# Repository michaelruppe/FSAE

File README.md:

# FSAE

Hardware projects for the FSAE Electric 2019/2020 competition (Australia).
💻Github https://github.com/michaelruppe/FSAE

## Resources
**Team mentoring and design reviews available - contact through [michaelruppe.com](https://michaelruppe.com)**

[ShutdownCircuit.com](https://shutdowncircuit.com) is a free resource to help new FSAE EV teams shortcut the growing pains of designing EV safety systems.

## [TSAL](TSALv3)
A light that indicates presence of dangerous voltage within the Tractive System

<div align="center">

<p>The third iteration of the TSAL driver. </p>
</div>

Watch a [video walkthrough](https://youtu.be/bgW9xbbovIY) explaining the circuit operation and design decision.

## [Precharge](Precharge)
A device to precharge the Tractive System. This prototype features voltage feedback to protect AIRs. In open-loop systems, if a wiring fault develops - eg. precharge resistor is disconnected - then the precharge is ineffective and AIRs may become damaged.
<div align="center">

<p>The prototype Precharge module</p>
</div>

 ## [HFL (Hard Fault Latch)](HFL)

 Latches momentary faults that are required to shutdown the EV.

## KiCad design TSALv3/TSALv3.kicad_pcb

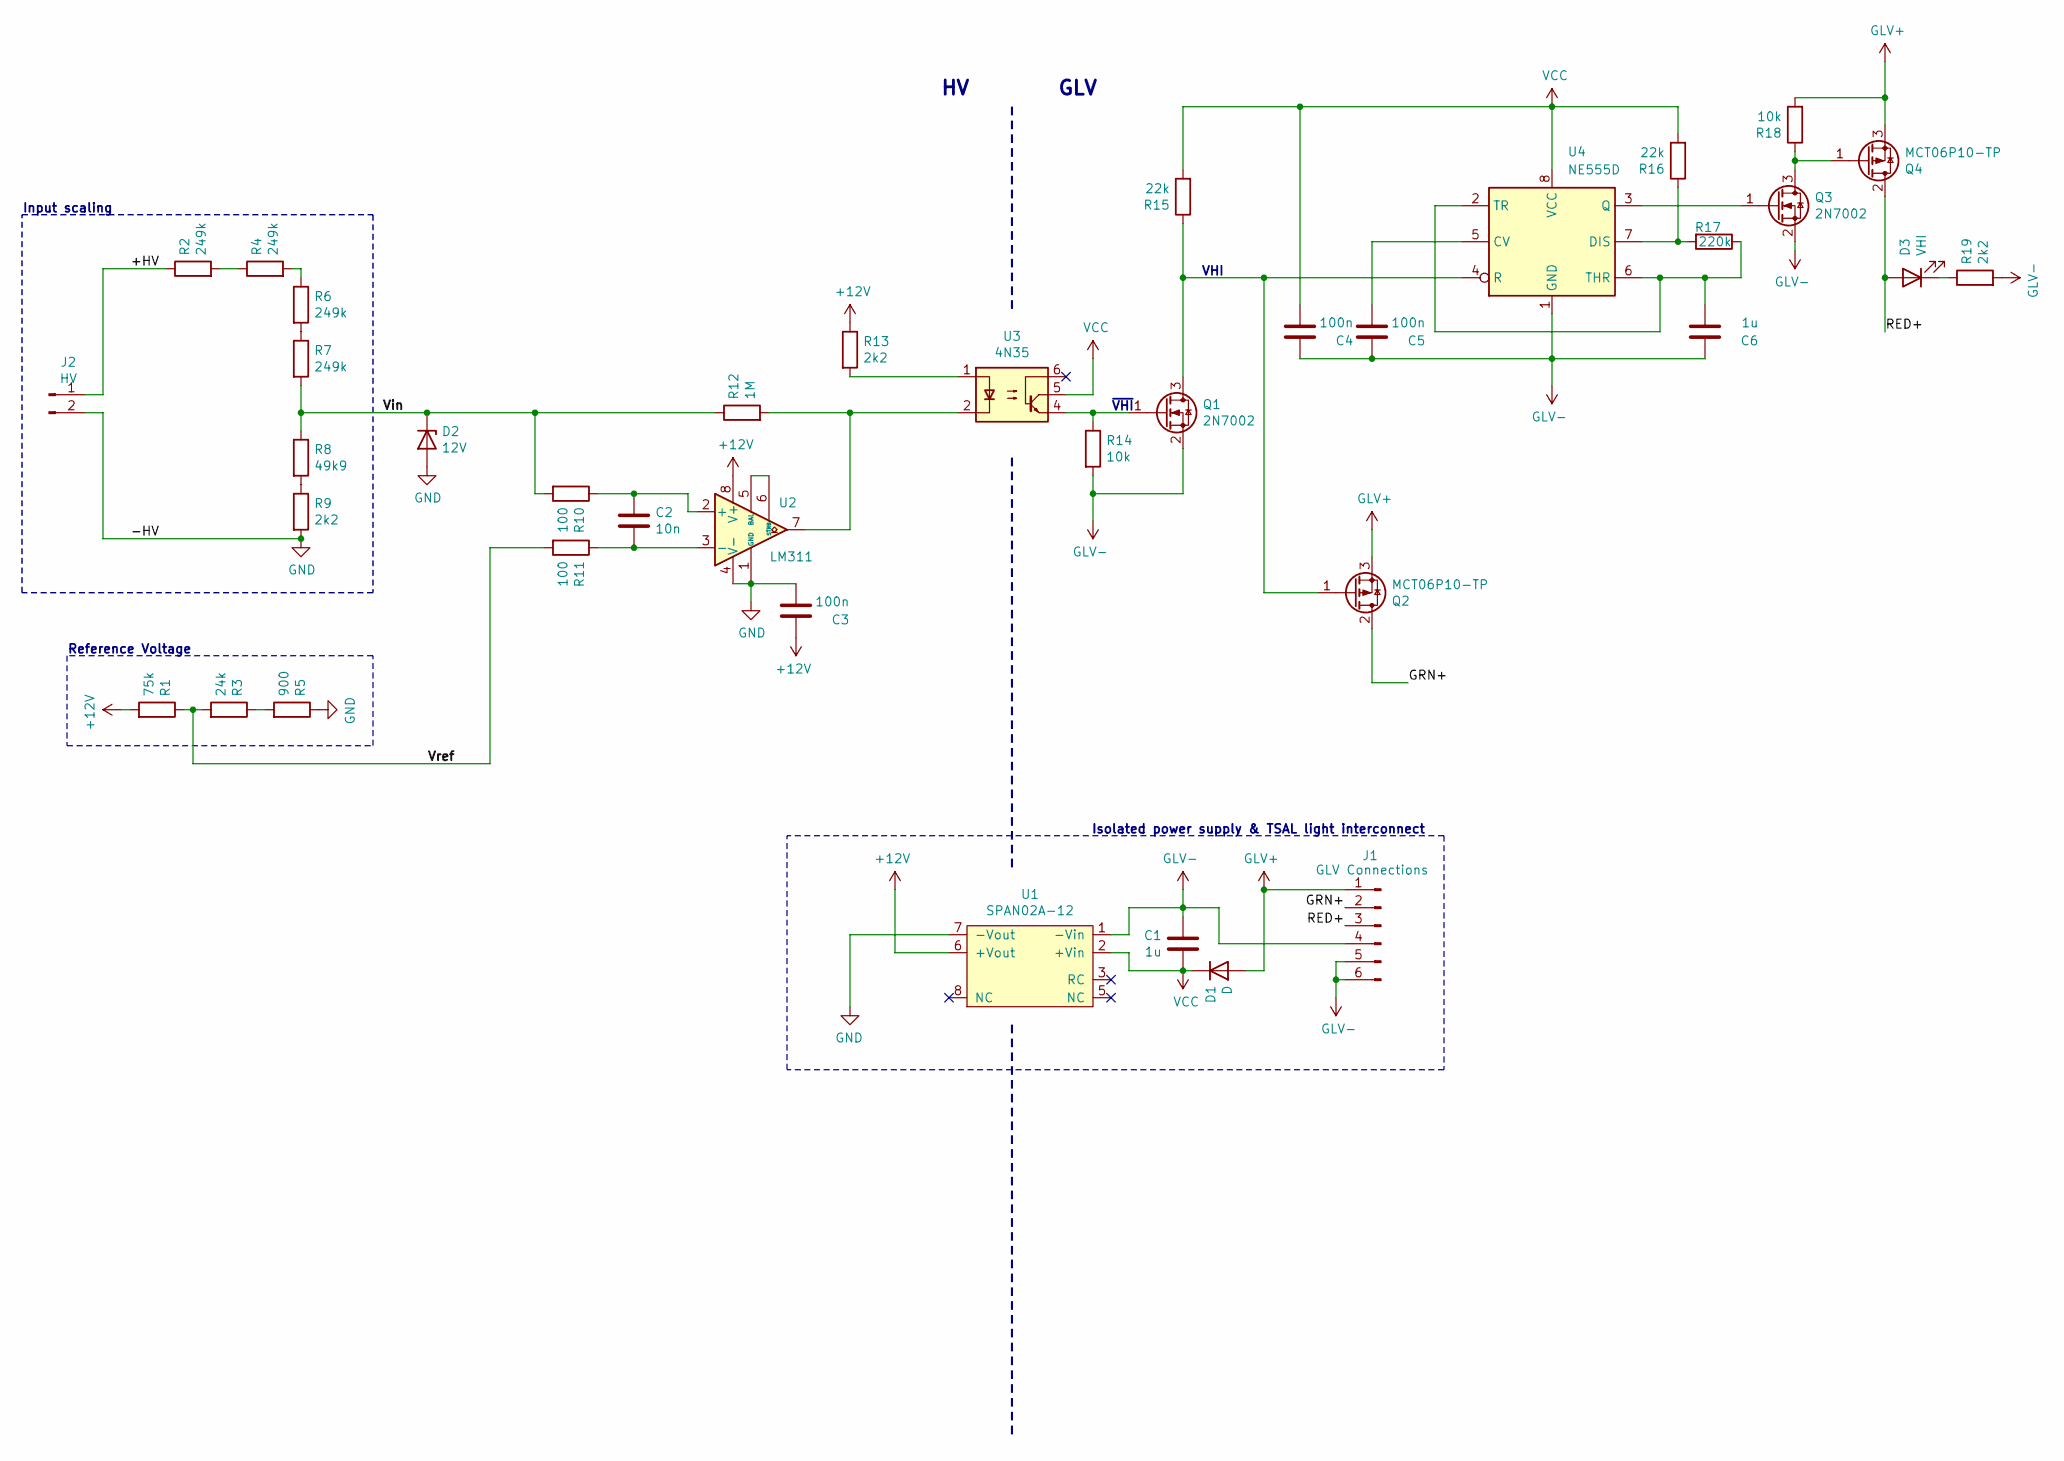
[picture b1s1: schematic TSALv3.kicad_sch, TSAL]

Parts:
C1, C6: 1u; C_0805_2012Metric_Pad1.15x1.40mm_HandSolder
C2: 10n; C_0805_2012Metric_Pad1.15x1.40mm_HandSolder
C3, C4, C5: 100n; C_0805_2012Metric_Pad1.15x1.40mm_HandSolder
D1: D; D_SMA
D2: 12V; D_DO-35_SOD27_P7.62mm_Horizontal
D3: VHI; LED_0805_2012Metric_Pad1.15x1.40mm_HandSolder
J1: GLV Connections; Molex_Micro-Fit_3.0_43045-0612_2x03_P3.00mm_Vertical
J2: HV; Molex_Mini-Fit_Jr_5566-02A_2x01_P4.20mm_Vertical
Q1, Q3: 2N7002; SOT-23
Q2, Q4: MCT06P10-TP; SOT-223-3_TabPin2
R1: 75k; R_1206_3216Metric_Pad1.42x1.75mm_HandSolder
R2, R4, R6, R7: 249k; R_1206_3216Metric_Pad1.42x1.75mm_HandSolder
R3: 24k; R_1206_3216Metric_Pad1.42x1.75mm_HandSolder
R5: 900; R_1206_3216Metric_Pad1.42x1.75mm_HandSolder
R8: 49k9; R_1206_3216Metric_Pad1.42x1.75mm_HandSolder
R9, R13, R19: 2k2; R_1206_3216Metric_Pad1.42x1.75mm_HandSolder
R10, R11: 100; R_1206_3216Metric_Pad1.42x1.75mm_HandSolder
R12: 1M; R_1206_3216Metric_Pad1.42x1.75mm_HandSolder
R14, R18: 10k; R_1206_3216Metric_Pad1.42x1.75mm_HandSolder
R15, R16: 22k; R_1206_3216Metric_Pad1.42x1.75mm_HandSolder
R17: 220k; R_1206_3216Metric_Pad1.42x1.75mm_HandSolder
U1: SPAN02A-12; SPAN02
U2: LM311; SOIC-8_3.9x4.9mm_P1.27mm
U3: 4N35; DIP-6_W7.62mm
U4: NE555D; SOIC-8_3.9x4.9mm_P1.27mm

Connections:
+12V: C3.1, R1.2, R13.1, U1.6 (+Vout), U2.8 (V+)
/+HV: J2.1, R2.1
/GRN+: J1.2, Q2.2 (D)
/RED+: D3.2 (A), J1.3, Q4.2 (D)
/Vin: D2.1 (K), R7.2, R8.1, R10.2, R12.1
/Vref: R1.1, R3.2, R11.2
GLV+: D1.2 (A), J1.1, Q2.3 (S), Q4.3 (S), R18.2
GLV-: C1.1, C4.1, C5.1, C6.1, J1.4, J1.5, J1.6, Q1.2 (S), Q3.2 (S), R14.2, R19.2, U1.1 (-Vin), U4.1 (GND)
GND: C3.2, D2.2 (A), J2.2, R5.1, R9.2, U1.7 (-Vout), U2.1 (GND), U2.4 (V-)
unnamed: C2.1, R10.1, U2.2 (+)
unnamed: C2.2, R11.1, U2.3 (-)
unnamed: C5.2, U4.5 (CV)
unnamed: C6.2, R17.1, U4.2 (TR), U4.6 (THR)
unnamed: D3.1 (K), R19.1
unnamed: Q1.1 (G), R14.1, U3.4
unnamed: Q1.3 (D), Q2.1 (G), R15.1, U4.4 (R)
unnamed: Q3.1 (G), U4.3 (Q)
unnamed: Q3.3 (D), Q4.1 (G), R18.1
unnamed: R2.2, R4.1
unnamed: R3.1, R5.2
unnamed: R4.2, R6.1
unnamed: R6.2, R7.1
unnamed: R8.2, R9.1
unnamed: R12.2, U2.7, U3.2
unnamed: R13.2, U3.1
unnamed: R16.1, R17.2, U4.7 (DIS)
unnamed: U2.5 (BAL), U2.6 (STRB)
VCC: C1.2, C4.2, D1.1 (K), R15.2, R16.2, U1.2 (+Vin), U3.5, U4.8 (VCC)

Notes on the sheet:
VHI
Isolated power supply & TSAL light interconnect
Reference Voltage
GLV
~{VHI}
Input scaling

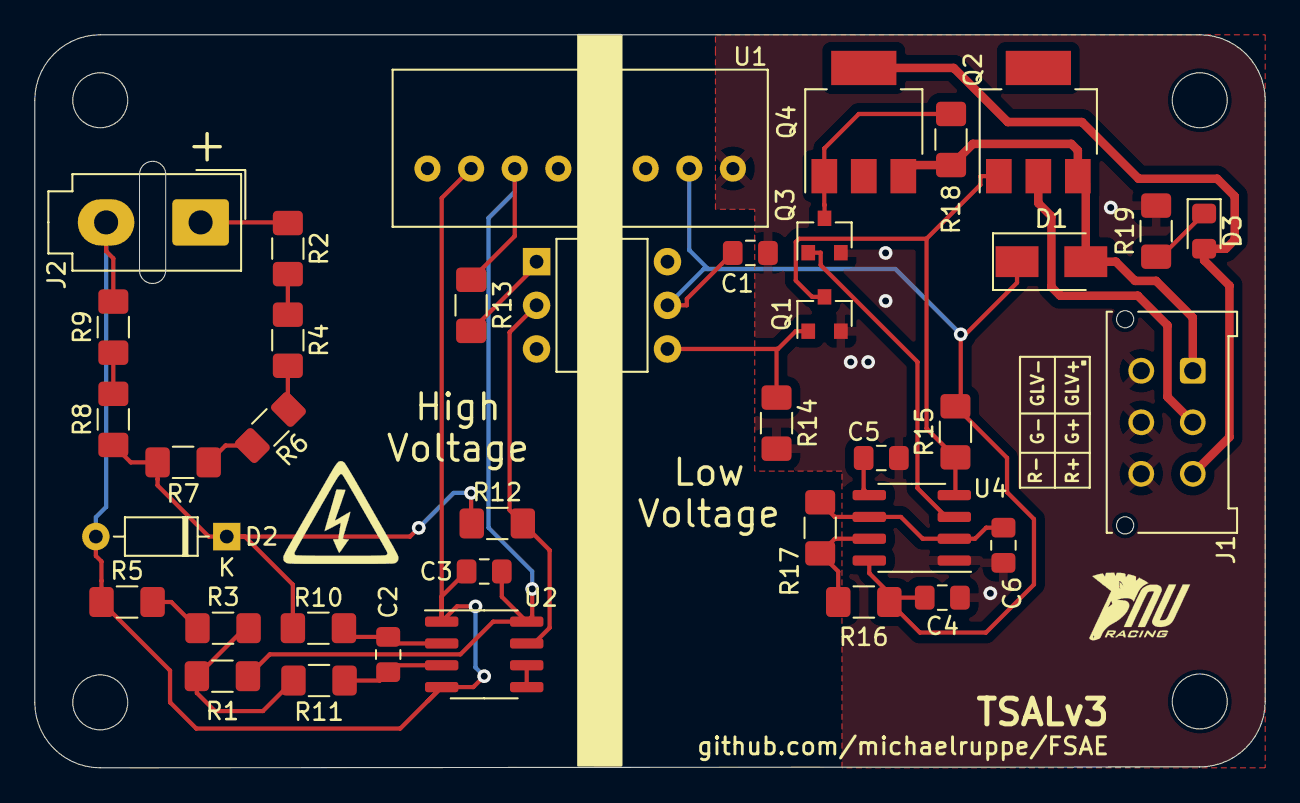
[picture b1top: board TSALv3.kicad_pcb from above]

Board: 2 copper layers, 71.6 x 42.7 mm, 42 parts (0 on the bottom side), 28 nets.

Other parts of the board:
MH1, MH2, MH3, MH4: MountingHole_3.2mm_M3

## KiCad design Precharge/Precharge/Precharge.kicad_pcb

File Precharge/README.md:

# Precharge

**[Watch the walkthrough video](https://www.youtube.com/watch?v=6-RndXZ5mR4)**

A device to precharge the Tractive System. This prototype features voltage feedback to protect AIRs. In open-loop systems, if a wiring fault develops (eg. precharge resistor is disconnected or discharge is stuck on) then the precharge is ineffective and AIRs may become damaged.
<div align="center">

<p>Figure 1: The prototype Precharge module</p>
</div>

**Important Directories / Files**
- [code/precharge](code/precharge) - The source code
- [docs/schematic-v1.1.pdf](docs/schematic-v1.1.pdf) - The schematic, as built.
- [docs/pinout-v1.1.pdf](docs/pinout-v1.1.pdf) - Pinout diagram with connection descriptions.
- [docs](docs) - Data collected during commissioning, image assets for this document.
- [Precharge](Precharge) - The PCB design files

## Contents

- [Specifications and Features](#Specifications-and-Features)
- [Operation](#Operation)
- [Commissioning Steps - Precharge](#Commissioning-Steps-Precharge)
  - [Characterise Voltage-Frequency Relationship](Characterise-Voltage-Frequency-Relationship)
  - [Simulate Precharge](#Simulate-Precharge)
  - [Results](#Results)
- [Commissioning Steps - PDOC](#Commissioning-Steps-PDOC)
- [How to modify this design](#How-to-modify-this-design)
- [Recommendations](#Recommendations)

## Specifications and Features
- Wide input voltage 0 - 600V
- Powered by shutdown circuit: 12V
- Integrated PDOC
- Isolated HV measurement
- CAN interface (provisional) for status output
- Serial interface for status and commissioning data
- FSAE one-size-fits-all. This module is capable of precharging any voltage accumulator (within FSAE rules) without significant hardware/software rework. To modify for a new accumulator/tractive-system, select appropriate precharge resistor and update relevant software parameters, discussed in [How to modify this design](#How-to-modify-this-design)

## Operation
A brief description of the Precharge logic follows. Refer to *Figures 2 & 3* for state-flow information.
- Initialise in `State: Standby` and monitor for a stable Shutdown Circuit.
- If Shutdown Circuit is stable, enter `State: Precharge`:
  - Close the precharge relay
  - Monitor Accumulator voltage and Tractive System voltage
  - Once TSV is close enough to AV (eg >95%), precharge is complete
  - If precharge is too fast or too slow, a fault is likely present eg. Wiring fault, discharge stuck-on, stuck relay.
- If precharge completed with no errors, proceed to `State: Online`:
  - Enable the AIR, open precharge relay

If at any point the Shutdown Circuit voltage becomes too low, enter `State: Standby`

<div align="center">

<p>Figure 2: A top-level look at the state-flow behaviour</p>
</div>
<div align="center">

<p>Figure 3: precharge sequence timing. When the TS voltage reaches the target voltage, precharge is complete and the AIR closes. The target voltage should be 90-95% of the Accumulator voltage</p>
</div>

## Commissioning Steps - Precharge
*Refer to the [docs/schematic-v1.1](docs/schematic-v1.1.pdf) for component and test-point references.*

*Refer to [docs/Experiments.xlsx](docs/Experiments.xlsx) for sample data collected during prototype construction.*

This section describes the steps taken to construct and characterise the Precharge Module. Repeat these steps as necessary when re-commissioning later versions of the circuit.

### Characterise Voltage-Frequency Relationship
- Assemble power supply components and V-F converter circuitry `U5 - U9`.
- Characterise voltage-frequency performance: perform V-F experiment `code/01-v-f-experiment` *Refer to Figure 4 for sample data collected during prototype construction*
  - Apply 0.15-10V at V-F inputs: `TP5, TP6`.
  - Record output frequencies: `TP1, TP2` vs input voltages.
  - Create linear fit and record the gain and offset parameters.
  - Update [code/precharge/measurements.cpp](code/precharge/measurements.cpp) with the linear-fit parameters: `V2F_slope_accu, V2F_ofs_accu, V2F_slope_ts, V2F_ofs_ts`
- If resistors `R31,R32,R36-39` or `R33,R34,R40-R3` are different to schematic:
  - Find the gain of these voltage dividers: eg `Gain = R39/(R31+R32+R36+R37+R38+R39)`
  - Update [code/precharge/measurements.cpp](code/precharge/measurements.cpp): `gainVoltageDivider` with the new gain value.

  <div align="center">
  
  <p>Figure 4: Results from the V-F experiment - data collected from the prototype during construction. The V-F response is extremely linear. Expect f(0V) = 0Hz, which is supported by very small y-intercept constants. While the V-F converter circuits are nominally identical, they should be characterised separately to account for component tolerance.</p>
  </div>

### Simulate Precharge
Here, we simulate a precharge sequence using low voltages that bypasses the prescaling voltage dividers.

<div align="center">

<p>Figure 5: Simulate a precharge sequence using a low voltage. The prescaling voltage dividers are bypassed by connecting Testpoint:TP5 to the switched accumulator voltage; and Testpoint:TP6 to the HV OUT connector.
</p>
</div>

*Voltages listed are referenced to the `GNDS` net, connector `J3` labelled `TS-`*
- Connect a known capacitive load eg 1000uF to `HV OUT`. Include a large parallel resistance (eg 20k) for capacitor discharge.
  - The voltage divider created by this resistance and the precharge resistor `R46` will limit the maximum voltage seen at capacitor. Large resistances will reduce this effect, but the capacitor will discharge more slowly during this test.
- Bypass the prescaling voltage dividers:
  - Connect `TP5` to precharge resistor (accumulator side)
  - Connect `TP6` to `HV OUT`
- Apply 4-10V to `HV IN`. Exact voltage will depend on accumulator voltage to be simulated: Accumulator Voltage multiplied by `gainVoltageDivider` (0.015 from prescribed components) gives this voltage.
- Monitor serial data from the microcontroller via USB
- Power the circuit at `J1`
- Monitor precharge behaviour in serial console and note precharge percentage and duration.
- Modify and upload [code/precharge/precharge.ino](code/precharge/precharge.ino) as necessary. Relevant parameters are:
  - `MIN_EXPECTED`[ms] The minimum allowable precharge time. Times faster than this are likely due to wiring fault.
  - `MAX_EXPECTED`[ms] The maximum allowable precharge time. Times slower than this are likely due to wiring fault, stuck discharge circuit.
  - `TARGET_PERCENT`[%] Precharge to this percentage of accumulator voltage.
    - The discharge resistance used during this simulation affects the maximum TS voltage attainable. I found a maximum voltage of only 90% when using Precharge:390Ohm and discharge 4k7.

### Results
A precharge sequence was simulated following the above procedure with results shown in *Figure 6*. Simulated voltages were measured accurate to the nearest volt.

**Parameters:**
- V Accumulator: 5.05V (336V equivalent)
- Tractive system capacitor: 1000uF
- Tractive system discharge capacitor: 4k7 (connected in parallel with capacitor. Larger value as in Figure 5 is preferred)
- `gainVoltageDivider`= 0.015 ([code/precharge/measurements.cpp](code/precharge/measurements.cpp))
- Target precharge percentage: 88.0 (discharge resistor is only one order of magnitude larger than 390Ohm precharge resistor)

<div align="center">

<p>Figure 6: Results from a simulated precharge. Here, the accumulator was simulated with 5.05V => 337Vequiv. The TS voltage at TP6 reached 4.561V => 304Vequiv. which is 90.2% as indicated. The precharge finished at 90% instead of 88% because some settling time is imposed by the program.
</p>
</div>

Of note are the seemingly high precharge percentages observed between 0-200ms. These are artifacts of moving average filters used to smooth voltage measurements and reject spurious measurements. Since the smoothed accumulator voltage does not rise instantaneously, the precharge voltage represents a significant percentage in early stages of the precharge cycle.

## Commissioning Steps - PDOC
The Precharge module includes an integrated thermal overload protection (PDOC) (Figure 7). A thermistor `TH1` monitors the precharge resistor temperature. As temperature increases, the inverting-input voltage of comparator `U10A` rises. Once the voltage at the inverting input rises above the reference voltage (noninverting input) the PDOC will trip. The reference voltage created by `R26` and `R27` therefore sets the temperature threshold. If `R27` = `R29` then select `R26` to be equal to the value of `TH1` at the desired trip-temperature. Referring to thermistor data in Figure 8, for a trip-temperature of eg. 80 degC, `R26` should be about 12kOhm.

<div align="center">

<p>Figure 7: The Precharge Overload Circuit monitors the temperature of the precharge resistor and triggers a fault if the temperature becomes too high. R26,R27 set the threshold temperature, TH1 is the temperature-monitoring thermistor.
</p>
</div>

<div align="center">

<p>Figure 8: The thermistor response. R_25 is 10kOhm for the selected device. At 80 degrees Celcius the resistance will be 1.242 x 10kOhm = 12.4kOhm
</p>
</div>

## How to modify this design
When moving to a new tractive system configuration and/or accumulator voltage, the only hardware component that may require respecification is the Precharge Resistor `R46`. A HS25 series resistor ([datasheet](datasheets/TE-Connectivity-Type-HS-Series-Resistor-1773035_C)) from TE Connectivity is specified for this component - available in a large range of resistances. As per the datasheet, these devices are capable of short-duration overloads many times in excess of their continuous-duty rating. It is likely that only the resistance will need to be respecified, ie. select a  HS25 family resistor of the appropriate resistance.

<div align="center">

<p>Short term overloading of a power resistor is acceptable. This design relies on short term overloading to keep the power resistor small, light and cheap.
<br>(Graphic Source: TE Connectivity Type HS datasheet)
</p>
</div>

In 2020, NU Racing specified a 400V accumulator and a TS capacitance of 1600uF. Using these as design constraints, a 390Ohm precharge resistor was selected to precharge the TS quickly without excessive overload. As seen below, the resistor is overloaded to 400W (16 times its rating) for a very brief period at the start of a precharge sequence. After approximately 1 second the resistor is no longer overloaded. The initial precharge current(~1A) is well within the capacity of the precharge contactor. The resistance is above the minimum required for 2020 motorcontrollers (47 Ohm).

<div align="center">

<p>A 390Ohm 25W resistor precharges the TS to 95% in about 2.5 seconds, experiencing a brief 16x overload. Overloads of this nature are acceptable for the selected family of power resistors and allow cheaper, smaller, low-power resistors to be specified.
</p>
</div>

Once the appropriate resistor has been selected, follow the [Simulate Precharge](#Simulate-Precharge) steps to identify any software parameters that require modification.

## Recommendations & ToDo

**V-F Conversion**: Either include offset in V-F converter circuit so that min frequency is eg ~100Hz instead of 0Hz ([Datasheet](https://www.ti.com/lit/ds/symlink/lm331.pdf): Figure 14) or replace V-F converters with a microcontroller programmed for the same task. The challenge is that low frequencies require a long timeout period. Applying a 100Hz offset means the longest timeout would be 10 milli-seconds. The current solution works well, using a combination of outlier rejection and Exponential Moving Average filters.

**PCB**:
The footprint assigned to the 4N35 optocouplers is slightly off. Serviceable, but not perfect. Consider re-assigning the footprint.

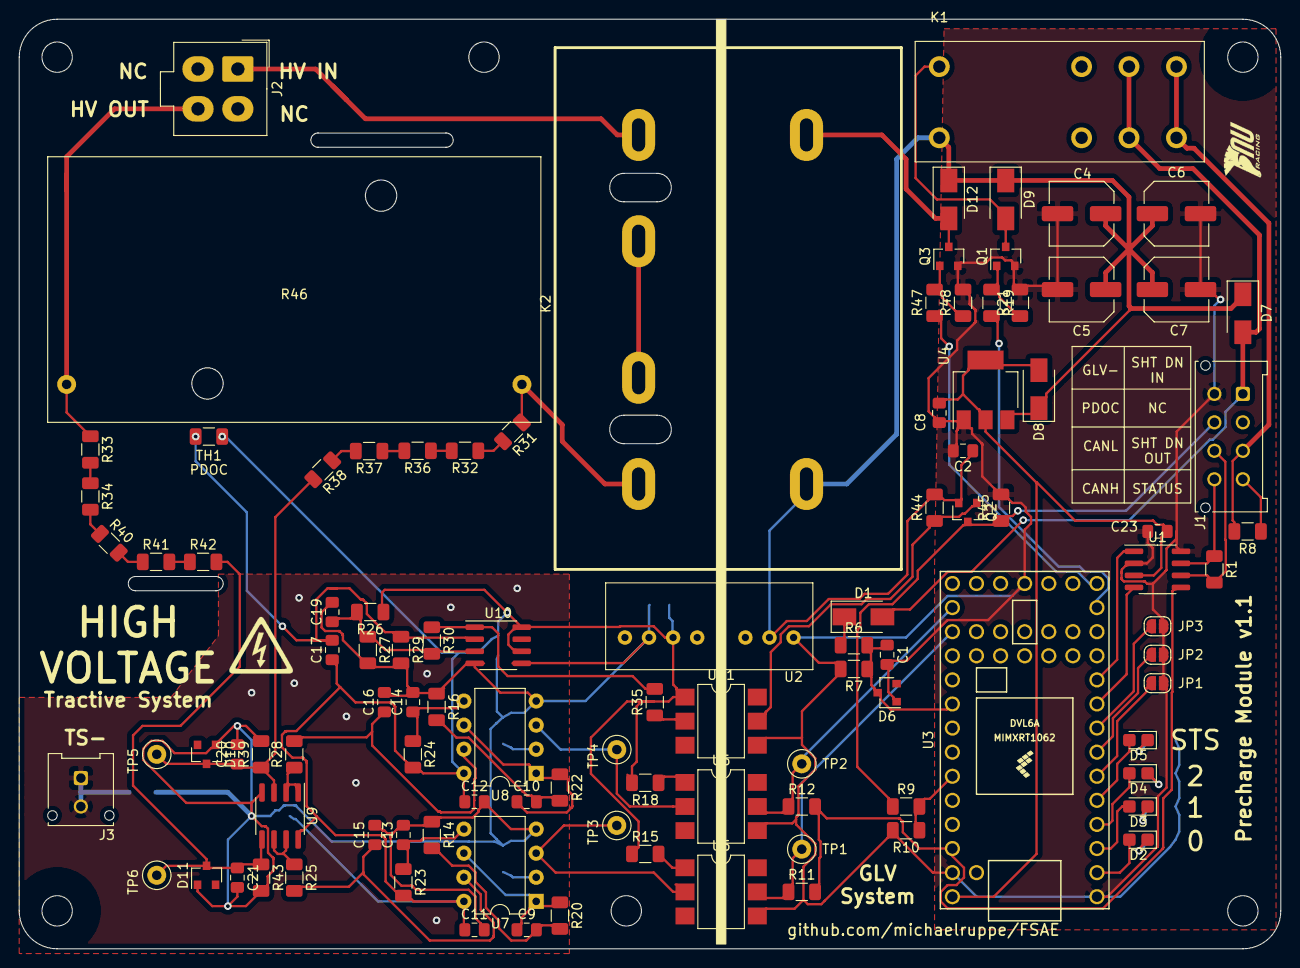
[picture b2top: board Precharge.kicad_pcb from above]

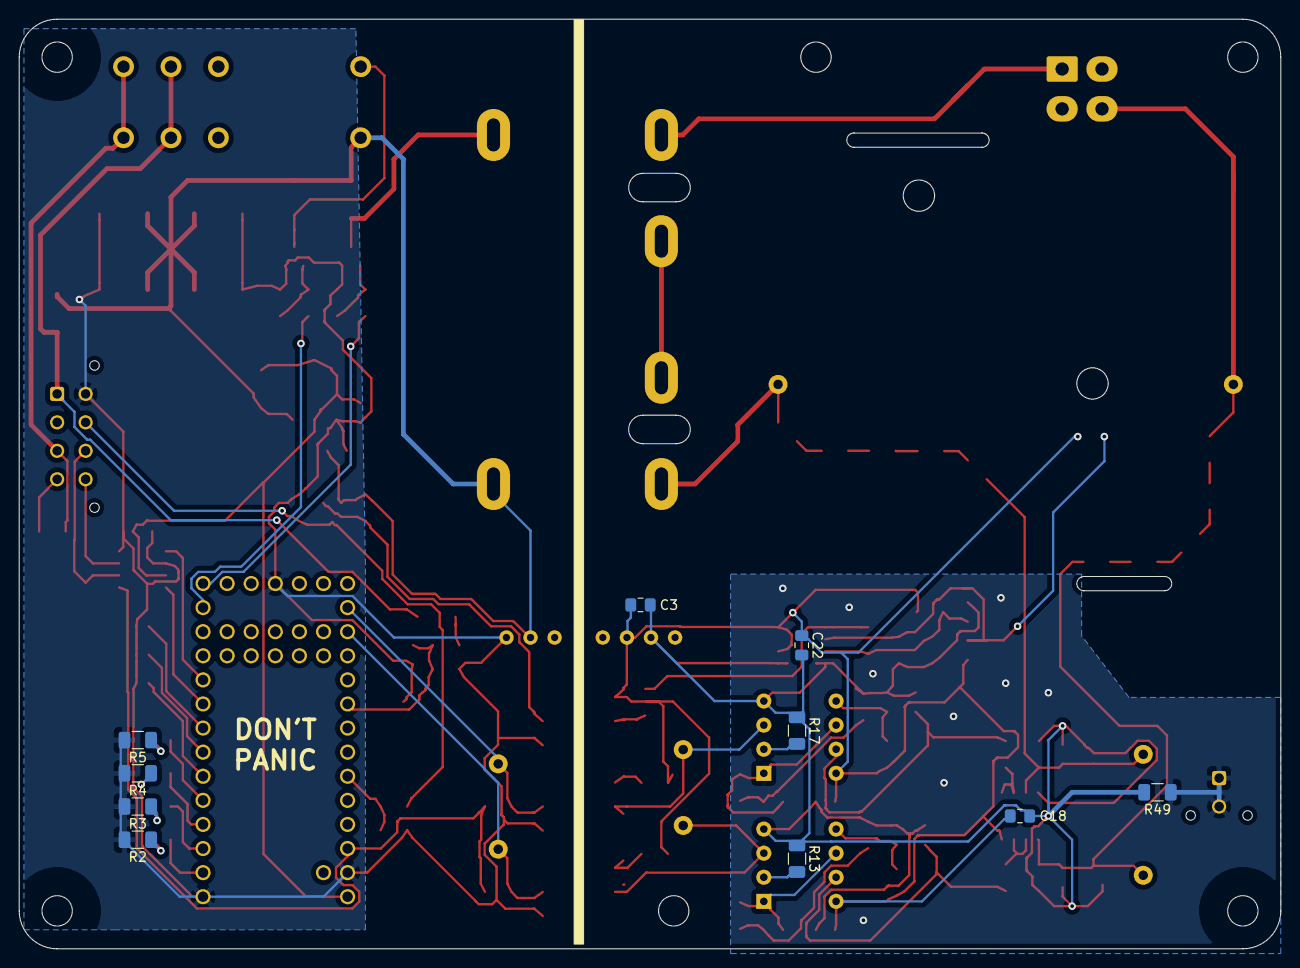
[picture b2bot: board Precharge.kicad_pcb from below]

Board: 2 copper layers, 133.0 x 98.0 mm, 119 parts (10 on the bottom side), 72 nets.

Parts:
C1, C2, C11, C12, C15, C16, C17, C18, C19, C20, C21, C22, C23: 100n; C_0805_2012Metric_Pad1.15x1.40mm_HandSolder
C3, C8, C9, C10: 1u; C_0805_2012Metric_Pad1.15x1.40mm_HandSolder
C4, C5, C6, C7: 220u; C_Elec_6.3x5.4
C13, C14: 10n; C_0805_2012Metric_Pad1.15x1.40mm_HandSolder
D1, D7, D8, D9, D12: D; D_SMA
D2, D3, D4, D5: LED; LED_0805_2012Metric_Castellated
D6: BZX84C3V3; D_SOT-23_ANK
D10, D11: BZX84C12; D_SOT-23_ANK
J1: MicroFit; Molex_Micro-Fit_3.0_43045-0812_2x04_P3.00mm_Vertical
J2: Mini-Fit_Jr_5566-04A; Molex-Mini-Fit-Jr-4-pin-P4.2mm-RowP4.2mm
J3: Micro-Fit 43045-0212; Molex_Micro-Fit_3.0_43045-0212_2x01_P3.00mm_Vertical
JP1, JP2, JP3: SolderJumper_2_Open; SolderJumper-2_P1.3mm_Open_RoundedPad1.0x1.5mm
K1: OMRON-G2RL-24; OMRON-G2R-24
K2: G7L-2A-X-L
MT1, MT2, MT3, MT4, MT5, MT6: MountingHole_3.2mm_M3
Q1, Q3: 2N7002; SOT-23
Q2: MMBT3906; SOT-23
R1: 160; R_1206_3216Metric
R2, R3, R4, R5: 200; R_1206_3216Metric
R6, R9: 20k; R_1206_3216Metric
R7, R10, R23, R24: 6k8; R_1206_3216Metric
R8, R21, R26, R27, R29, R44, R45, R48: 10k; R_1206_3216Metric
R11, R12: 1k5; R_1206_3216Metric
R13, R17: 12k; R_1206_3216Metric
R14, R16: 47; R_1206_3216Metric
R15, R18: 560; R_1206_3216Metric
R19, R47: 220; R_1206_3216Metric
R20, R22, R25, R28: 100k; R_1206_3216Metric
R30: 500k; R_1206_3216Metric
R31, R32, R33, R34, R36, R37, R38, R40, R41, R42: 510k; R_1206_3216Metric
R35: 2k2; R_1206_3216Metric
R39, R43: 39k; R_1206_3216Metric
R46: HSA25390RJ; Chassis_Resistor_TE_Connectivity_HSA25
R49: 0; R_1206_3216Metric
TH1: TFPT1206L1002FM; R_1206_3216Metric
TP1, TP2, TP3, TP4, TP5, TP6: TestPoint; TestPoint_Loop_D2.50mm_Drill1.0mm_LowProfile
U1: TJA1051T-3; SOIC-8_3.9x4.9mm_P1.27mm
U2: SPAN02A-12; SPAN02
U3: Teensy4.0; Teensy40
U4: LM1117-5.0; SOT-223-3_TabPin2
U5, U6, U11: 4N35; SMDIP-6_W7.62mm
U7, U8: LM331; DIP-8_W7.62mm
U9: LM2904; SOIC-8_3.9x4.9mm_P1.27mm
U10: LM393; SOIC-8_3.9x4.9mm_P1.27mm

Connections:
+3V3: R11.2, R12.2, U1.5, U3.31
+5V: C8.1, C23.2, D8.2, U1.3, U3.33, U4.2
+12P: C3.2, C11.1, C12.1, C17.1, C18.1, C22.1, R15.1, R18.2, R23.2, R24.2, R26.1, TH1.2, U2.6, U7.8, U8.8, U9.8, U10.6, U10.8, U11.1
+12V: C2.1, C4.1, C5.1, C6.1, C7.1, D7.1, D8.1, D9.1, D12.1, K1.8, K2.0, Q2.2, R44.2, U2.2, U4.3
/CANH: J1.8, R1.1, U1.7
/CANL: J1.7, R1.2, U1.6
/CANRX: U1.4, U3.9
/CANTX: U1.1, U3.10
/CFG0: JP1.1, U3.6
/CFG1: JP2.1, U3.7
/CFG2: JP3.1, U3.8
/Faccu: R12.1, TP2.1, U3.21, U6.5
/FoutAccu: TP4.1, U6.2, U8.3
/FoutTS: TP3.1, U5.2, U7.3
/Fts: R11.1, TP1.1, U3.22, U5.5
/PDOC_OK: J1.6, Q2.3, R9.1, R45.1
/PRECHG: R47.1, U3.14
/PRECH_STS: J1.4, R8.1
/PWR_OK: C1.1, D6.1, R6.2, R7.1, U3.25
/SHTDN_CTRL: R19.2, U3.13
/SHTDN_OUT: J1.3, K1.4, K1.5, R8.2
/TS-: J3.1, J3.2, R49.1
/VinAccu: K2.2, R31.1, R46.1
/VinTS: J2.4, R33.1, R46.2
GLV+: D1.2, D7.2, J1.1, K1.3, K1.6
GLV-: C1.2, C2.2, C4.2, C5.2, C6.2, C7.2, C8.2, C23.1, D6.2, J1.5, JP1.2, JP2.2, JP3.2, Q1.2, Q3.2, R2.2, R3.2, R4.2, R5.2, R7.2, R10.2, R21.2, R45.2, R48.2, U1.2, U1.8, U2.1, U3.1, U3.17, U3.32, U4.1, U5.4, U6.4, U11.4
GNDS: C3.1, C11.2, C12.2, C13.2, C14.2, C15.2, C16.2, C18.2, C19.2, C20.2, C21.2, C22.2, D10.2, D11.2, R13.1, R14.1, R16.1, R17.1, R27.2, R29.2, R39.2, R43.2, R49.2, U2.7, U7.4, U8.4, U9.4, U10.4, U10.5
unnamed: C9.1, R20.1, U7.1, U7.6
unnamed: C9.2, R14.2, R20.2
unnamed: C10.1, R22.1, U8.1, U8.6
unnamed: C10.2, R16.2, R22.2
unnamed: C13.1, R23.1, U7.5
unnamed: C14.1, R24.1, U8.5
unnamed: C15.1, R25.2, U7.7
unnamed: C16.1, R28.2, U8.7
unnamed: C17.2, R29.1, TH1.1, U10.2
unnamed: C19.1, R26.2, R27.1, R30.2, U10.3
unnamed: C20.1, D10.1, R38.2, R39.1, TP5.1, U9.3
unnamed: C21.1, D11.1, R42.2, R43.1, TP6.1, U9.5
unnamed: D1.1, R6.1
unnamed: D2.1, R2.1
unnamed: D2.2, U3.2
unnamed: D3.1, R3.1
unnamed: D3.2, U3.3
unnamed: D4.1, R4.1
unnamed: D4.2, U3.4
unnamed: D5.1, R5.1
unnamed: D5.2, U3.5
unnamed: D9.2, K1.1, Q1.3
unnamed: D12.2, K2.1, Q3.3
unnamed: J2.1, K2.8
unnamed: K2.4, K2.6
unnamed: Q1.1, R19.1, R21.1
unnamed: Q2.1, R44.1, U11.5
unnamed: Q3.1, R47.2, R48.1
unnamed: R9.2, R10.1, U3.28
unnamed: R13.2, U7.2
unnamed: R15.2, U5.1
unnamed: R17.2, U8.2
unnamed: R18.1, U6.1
unnamed: R25.1, U9.6, U9.7
unnamed: R28.1, U9.1, U9.2
unnamed: R30.1, R35.2, U10.1
unnamed: R31.2, R32.1
unnamed: R32.2, R36.1
unnamed: R33.2, R34.1
unnamed: R34.2, R40.1
unnamed: R35.1, U11.2
unnamed: R36.2, R37.1
unnamed: R37.2, R38.1
unnamed: R40.2, R41.1
unnamed: R41.2, R42.1

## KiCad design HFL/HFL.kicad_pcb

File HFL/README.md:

**Warning: This design was never physically prototyped. As-is it is a mostly-complete design, but has never been through build, commissioning, troubleshooting. Proceed at your own risk.**

# Hard Fault Latch
A shutdown-circuit component.

The **Hard Fault Latch (HFL)** is a device that breaks the *Shutdown Circuit* when a *Hard Fault* is detected. These are faults generated by the IMD, BMS, BSPD PDOC-temperature, and BOTS. A Hard Fault is any fault that will deactivate the Tractive System, and cannot be reset by the driver.
The HFL is built upon relay-logic because it is easy to understand, reliable and hardened against noise and voltage transients.

An operator must press the HFR button each time the vehicle is powered-on, before the Tractive System can be activated.

Additionally, the HFL passes hard-fault statuses for the IMD, BMS, BSPD and PDOC (**not** BOTS) to the CCU for logging and dash-display.

# Technical Specifications
**ToDo**

# Design Justification
The final output relay must be capable of carrying sufficient current to power an AIR, and be a DPDT type. The smallest readily-available relay found was an OMRON G2R which is rated for 5A.

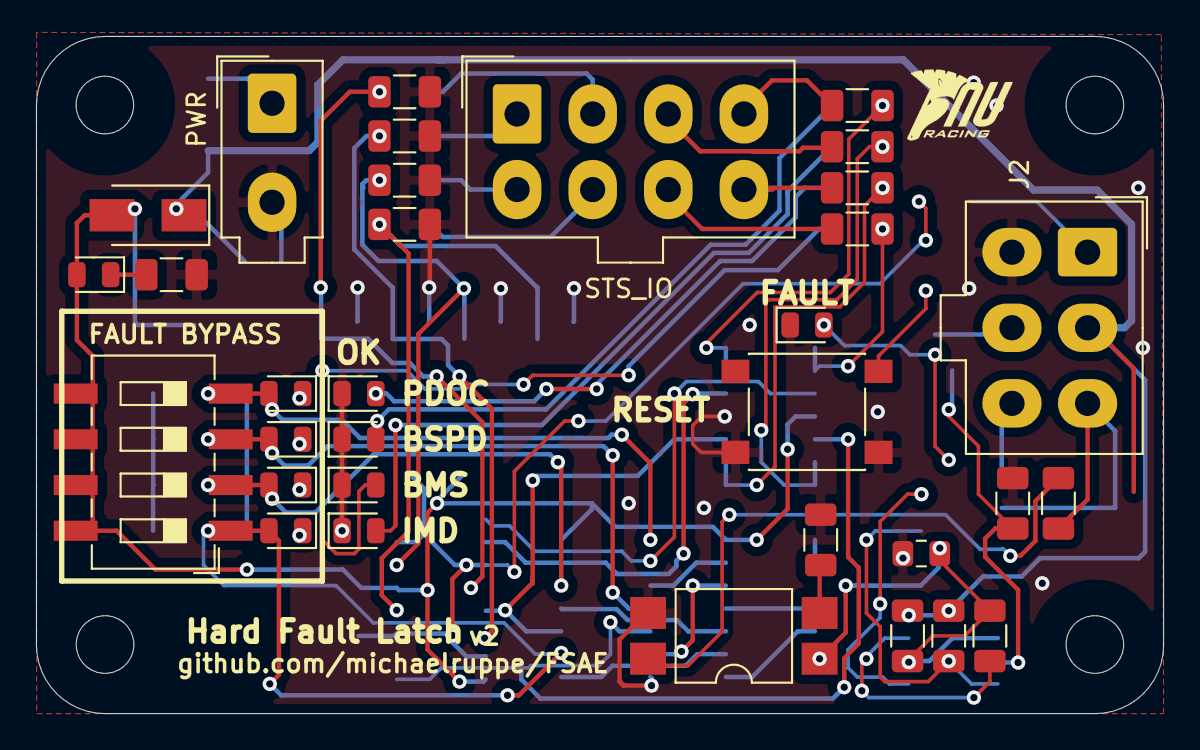
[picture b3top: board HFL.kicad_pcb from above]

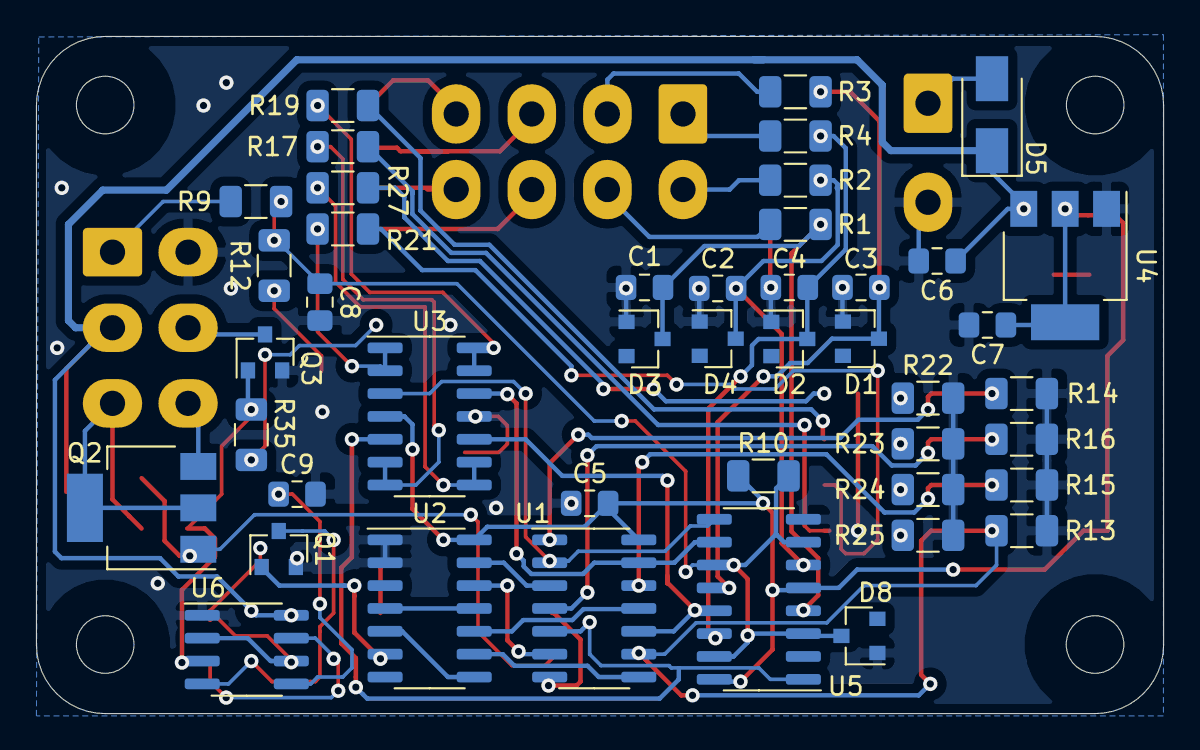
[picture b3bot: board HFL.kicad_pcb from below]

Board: 2 copper layers, 62.6 x 37.6 mm, 77 parts (44 on the bottom side), 58 nets.

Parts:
C1, C2, C3, C4, C9: 10n; C_0805_2012Metric_Pad1.15x1.40mm_HandSolder
C5: 100n; C_0805_2012Metric_Pad1.15x1.40mm_HandSolder
C6, C7, C8, C10: 1u; C_0805_2012Metric_Pad1.15x1.40mm_HandSolder
D1, D2, D3, D4, D8: BZX84Cxx; D_SOT-23_ANK
D5, D6: D; D_SMA
D7: PWR; LED_0805_2012Metric
D9, D10, D12, D14: MAN; LED_0805_2012Metric
D11: IMD-OK; LED_0805_2012Metric
D13: BSPD-OK; LED_0805_2012Metric
D15: BMS-OK; LED_0805_2012Metric
D16: PDOC-OK; LED_0805_2012Metric
D17: FAULT; LED_0805_2012Metric
J1: STS_IO; Molex-Mini-Fit-Jr-8-pin-P4.2mm-RowP4.2mm
J2: Conn_01x06_Male; Molex-Mini-Fit-Jr-6-pin-P4.2mm-RowP4.2mm
J3: PWR; Molex_Mini-Fit_Jr_5566-02A_2x01_P4.20mm_Vertical
Q1, Q3: 2N7002; SOT-23
Q2: MCT06P10-TP; SOT-223-3_TabPin2
R1, R2, R3, R4, R35: 2k2; R_1206_3216Metric
R5, R6, R7, R8, R10, R29, R32, R33: 100k; R_1206_3216Metric
R9, R12, R18, R20, R26, R28, R30: 1k; R_1206_3216Metric
R11: 3k3; R_1206_3216Metric
R13, R14, R15, R16, R34: 10k; R_1206_3216Metric
R17, R19, R21, R27: 2k7; R_1206_3216Metric
R22, R23, R24, R25: 330; R_1206_3216Metric
R31: 150k; R_1206_3216Metric
SW1: RST; SW_Push_1P1T_NO_6x6mm_H9.5mm
SW2: BYPASS; SW_DIP_SPSTx04_Slide_6.7x11.72mm_W8.61mm_P2.54mm_LowProfile
U1: 74LS32; SOIC-14_3.9x8.7mm_P1.27mm
U2: 74LS08; SOIC-14_3.9x8.7mm_P1.27mm
U3: MCP6004; SOIC-14_3.9x8.7mm_P1.27mm
U4: LM1117-5.0; SOT-223-3_TabPin2
U5: 4044; SOIC-16_3.9x9.9mm_P1.27mm
U6: NE555; SOIC-8_3.9x4.9mm_P1.27mm
U7: LTV-817S; SMDIP-4_W9.53mm

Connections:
+5V: C5.1, C7.1, D6.2, D7.2, R10.1, SW2.5, SW2.6, SW2.7, SW2.8, U1.14, U2.14, U3.4, U4.2, U5.5, U5.16
+12V: C6.1, D5.1, D6.1, J2.2, R29.1, R32.1, U4.3, U6.8
/BMS-BPS: D10.2, R15.2, SW2.2, U1.12
/BMS-OK: U1.13, U3.12, U5.10
/BMS-OKHS: J1.2, R3.2
/BMS-OUT: J1.4, R20.2
/BMS-STS: U1.11, U2.10
/BSPD-BPS: D12.2, R16.2, SW2.3, U1.4
/BSPD-OK: U1.2, U3.3, U5.9
/BSPD-OKHS: J1.5, R2.2
/BSPD-OUT: J1.7, R26.2
/BSPD-STS: U1.3, U2.13
/IMD-BPS: D9.2, R13.2, SW2.1, U1.9
/IMD-OK: U1.5, U3.5, U5.1
/IMD-OKHS: J1.1, R4.2
/IMD-OUT: J1.3, R18.2
/IMD-STS: U1.6, U2.12
/PDOC-BPS: D14.2, R14.2, SW2.4, U1.1
/PDOC-OK: U1.10, U3.10, U5.13
/PDOC-OKHS: J1.6, R1.2
/PDOC-OUT: J1.8, R28.2
/PDOC-STS: U1.8, U2.9
FLTLAMP-: J2.5, Q3.3
GND: C1.2, C2.2, C3.2, C4.2, C5.2, C6.2, C7.2, C8.1, C9.2, C10.2, D1.2, D2.2, D3.2, D4.2, D8.2, D11.1, D13.1, D15.1, D16.1, D17.1, J2.4, J3.2, Q1.2, Q3.2, R5.2, R6.2, R7.2, R8.2, R11.2, R13.1, R14.1, R15.1, R16.1, R22.2, R23.2, R24.2, R25.2, R30.2, R34.2, SW1.2, U1.7, U2.1, U2.2, U3.11, U4.1, U5.8, U6.1, U7.3
HFR1: J2.1, R9.2
unnamed: C1.1, D3.1, R1.1, R5.1, U5.4
unnamed: C2.1, D4.1, R2.1, R6.1, U5.6
unnamed: C3.1, D1.1, R3.1, R7.1, U5.12
unnamed: C4.1, D2.1, R4.1, R8.1, U5.14
unnamed: C8.2, D8.1, R9.1, R10.2, R12.1, U5.3, U5.7, U5.11, U5.15
unnamed: C9.1, U6.5
unnamed: C10.1, R31.1, R32.2, U6.2, U6.6
unnamed: D5.2, J3.1
unnamed: D7.1, R11.1
unnamed: D9.1, R25.1
unnamed: D10.1, R24.1
unnamed: D11.2, R17.2
unnamed: D12.1, R23.1
unnamed: D13.2, R19.2
unnamed: D14.1, R22.1
unnamed: D15.2, R21.2
unnamed: D16.2, R27.2
unnamed: D17.2, R35.2
unnamed: Q1.1, U2.6, U7.1
unnamed: Q1.3, R29.2, U6.4
unnamed: Q2.1, R33.2, U7.4
unnamed: Q3.1, R34.1, R35.1, U6.3
unnamed: R12.2, SW1.1
unnamed: R17.1, R18.1, U3.6, U3.7
unnamed: R19.1, R20.1, U3.13, U3.14
unnamed: R21.1, R26.1, U3.1, U3.2
unnamed: R27.1, R28.1, U3.8, U3.9
unnamed: R30.1, U7.2
unnamed: R31.2, U6.7
unnamed: U2.5, U2.8
unnamed: U2.4, U2.11
SHTDN_IN: J2.3, Q2.2, R33.1
SHTDN_OUT: J2.6, Q2.3

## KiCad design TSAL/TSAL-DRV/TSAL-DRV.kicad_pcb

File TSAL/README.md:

# TSAL
A comparator-based TSAL design for FSAE Electric 2019
*This repo is for the design of a system required in the Formula SAE competition 2019, and so will use common nomenclature specified in the [2019 rules v2.1](http://www.fsaeonline.com/cdsweb/gen/DocumentResources.aspx)*

The *Tractive System Active Light* is a red/green indicator light that indicates the presence of high-voltage in the Tractive System. The following design for a TSAL driver is split across two modules. The High-Voltage Measurement module (HVM) and the Indicator Module (DRV). The HVM connects to the output of the AIRs, and is located in the accumulator housing. The HVM is responsible for detecting whether Tractive System voltage is above or below the safe threshold.

## System Overview

## High-Voltage Measurement (HVM)

The HVM is located in the accumulator and measures the TS-voltage. The status of the TS-voltage is output by a open-collector style output (switched relay contact to ground).

The HVM has been designed to mount above the IMD, using the same mounting-hole dimensions. This will likely require conformal coating of the board and an intermediate insulating material to meet regulation EV.6.1.5 and EV.6.1.7

The HVM is designed to **not** be user adjustable. Resistive dividers R1, R2, R3, R4 and R5, R6, R7 may be used to set the trigger threshold for the onboard comparator. As specified, the board should safely handle 400V at the HV inputs (untested). Diode D1 begins conducting when approximately 200V is present at HV inputs - effectively limiting the input voltage of the comparator.

### Pinout

| Parameter                  | Value             |
|----------------------------|-------------------|
| Max Voltage (HV+ - HV-)    | 200V DC           |
| Switching threshold (HVin) | 60V DC            |
| Supply Voltage             | 12V DC            |
| Output                     | Switched Contacts |
| HV < 60V                   | OPEN              |
| HV > 60V                   | CLOSED            |

### Assembly notes
Many parts of the v1 design are provisional.
**ToDo - assembly instructions**

### Design justification
A comparator circuit was chosen because they are relatively simple to design, are well understood and behave predictably.
An isolated power supply U1 is powered by the GLV (12V) and provides an isolated 12V supply for this circuit.

R1, R2, R3, R4 form an input voltage divider which scales the input (0-200V -> 0-12V). The voltage divider is split between multiple resistors to keep the voltage across each resistor manageable. Since each 1208 package is rated for 200VDC this topology is theoretically capable of measuring up to 400VDC. This range can be trivially increased with the addition of more resistors in the divider.

R5, R6, R7 form a resistive divider that provides a stable voltage reference of 3V for the comparator. A resistive divider was chosen over a zener voltage reference because the output of the DC-DC converter U1 should be accurate and stable enough for this application.

With the values chosen, the output of the comparator should be HIGH while input voltage is less than 60V. The output should be LOW for input voltages greater than 60V.

R9, R8, C2 form an input filter for the comparator which is prescribed in the LM311 datasheet. This prevents noise coupling from the output to the input.

R10 is included to provide hysteresis. Since hysteresis is symmetric in this circuit, it is chosen to be small so as not to significantly offset the actual switching threshold from the desired threshold.

N-Channel MOSFET, Q1 and relay K1 form the isolated output of the circuit. While the input voltage is less than 60V, R11 pulls-up the gate of Q1, energising the relay coil and closing the contacts. D3 is a status indicator and D4 is a flyback diode.

The action of Q1 is inverted in Q2 and Q3, which drive an on-board status indicator LED and an off-board status indicator respectively.

To comply with FSAE rules the voltage systems on board are galvanically isolated. The clearances on-board require it to be conformal coated.

### Failure Modes - Fail Unsafe
 - Should the output of comparator U2 become disabled, R12 will continually pull the gate of Q1 high, energising the relay coil and indicating that a safe voltage is present.
 - If J1 is disconnected the TSAL will continually indicate a safe voltage is present - regardless of whether this is true or not.

These failure modes are clearly undesirable but deemed an acceptable risk for a first-revision TSAL. No publicly available design was found from competing teams that addressed these limitations.
The reasons these modes are fail-unsafe is due to the action of the comparator: The particular comparator chosen (LM311) has an open-collector output which must be accompanied by a pullup resistor. Since the switching action of the comparator pulls the output low and is capable of driving a relay directly, a suggested improvement is to either drive the relay coil directly (which also inverts the output action). This would reduce the parts count, removing Q1 from the BOM and reduce the number of critical components. Alternatively, a comparator with a push-pull output could be selected and directly substituted for U2.

### Failure Modes - Fail Safe
 - Should the TSAL-HVM lose power, the coil of relay K1 will be de-energised and its contacts will open. This will continually signal that dangerous voltage is present in the Tractive System. While that may not necessarily be true, the implausible behaviour of the TSAL should alert engineers that a fault is present: Either the AIRs are stuck closed, the Tractive System capacitors are remaining charged or a fault is present in the TSAL. All of these plausible causes should warrant due caution.

### Recommendations
There is significant room for improvement of the TSAL-HVM as made clear by the failure modes listed above. Here I will outline a brief description of how one might address what I consider to be the most serious limitation: The tendency to indicate safe-voltage if the TSAL-HVM is disconnected from the Tractive System.

If one can assume that the Tractive System is always capacitive (large capacitors at the motor driver power-input) then the HVM may be redesigned to check for the presence of capacitance at its measurement terminals using the Grounded Specimen Test method.

## Indicator module (DRV)
The Indicator module is powered by the GLVS and controls the behaviour of the red/green TSAL. It is controlled by a single input which is pulled low by the action of the HVM. Each output channel is capable of several amps and should be suitable for driving 12V LED assemblies or even incandescent bulbs.

### Pinout

### Design Notes
The heart of the driver module is the complementary operation of the timer (U1) and the P-Channel MOSFET (Q1). The VHI signal effectively selects which of these components should be active.

When VHI (J2) is pulled to ground, Q1 switches on - driving VLO indicator LED (D2) and powering the offboard, green TSAL LEDs (J1). A low signal at VHI also holds the reset pin of the U1 low, disabling its output.

When VHI is floating (the output-relay on HVM is open), R2 pulls-up the gate of Q1, turning off Q1. The RESET pin of U1 is also pulled-up, activating U1 which oscillates at approx. 3Hz, oscillating Q2 which flashes VHI LED (D1) and the off-board red TSAL LEDs (J1).

Power to the TSAL-DRV is unregulated, since all components are sufficiently robust to handle power deviations from the expected 12V.

### Known issues
The two power MOSFETs are a little close together. So close in fact that they could feasibly touch given the tolerances of fasteners and 3.2mm drilled holes.
Nothing should be *immediately* damaged if the tabs of the MOSFETs touch. However, any difference in switching time will cause momentary high-current through both transistors whenever the state of VHI changes. This is because the MOSFET drains will be connected together so there will be a momentary current path from GLV+ through Q1, Q2, to ground during any overlap in switching time.

Operation of the red/green circuit blocks are not *strictly* ​complementary. It is feasible that some analogue voltage could be applied at VHI which would allow both red and green components of the TSAL to be active. This is not a concern under the prescribed operating conditions. The operation could trivially be made strictly complementary by including input conditioning to VHI.

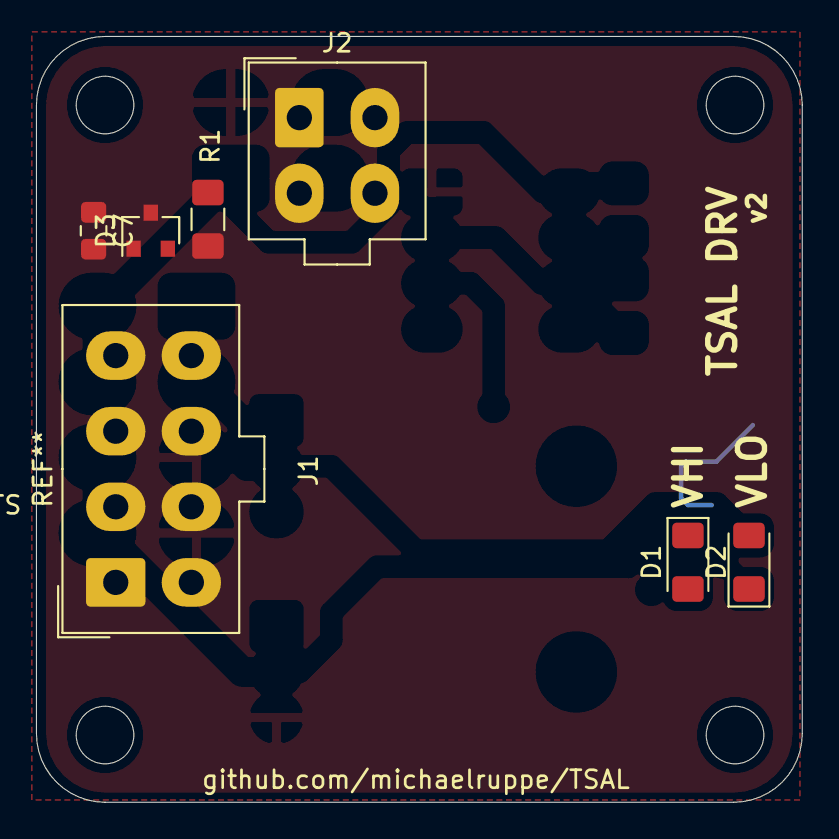
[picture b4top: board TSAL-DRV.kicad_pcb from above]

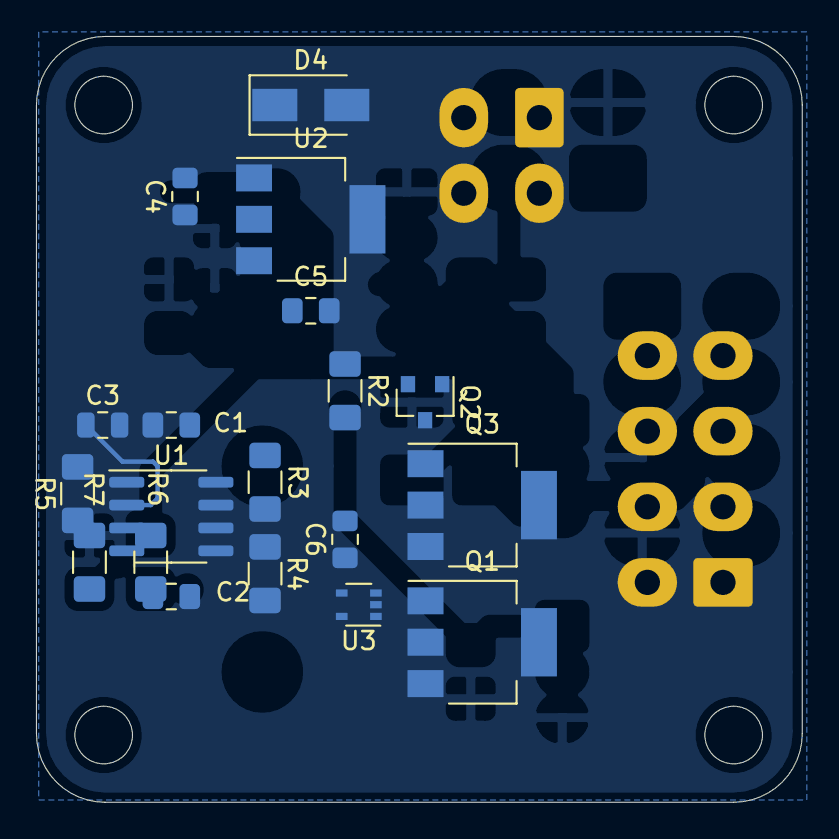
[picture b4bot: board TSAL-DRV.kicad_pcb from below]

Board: 2 copper layers, 42.5 x 42.5 mm, 26 parts (19 on the bottom side), 16 nets.

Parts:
C1, C6: 100n; C_0805_2012Metric_Pad1.15x1.40mm_HandSolder
C2, C7: 10n; C_0805_2012Metric_Pad1.15x1.40mm_HandSolder
C3: 1u; C_0805_2012Metric
C4, C5: 1u; C_0805_2012Metric_Pad1.15x1.40mm_HandSolder
D1: VHI; LED_1206_3216Metric_Pad1.42x1.75mm_HandSolder
D2: VLO; LED_1206_3216Metric_Pad1.42x1.75mm_HandSolder
D3: BZX84C5V1; D_SOT-23_ANK
D4: D; D_SMA
J1: Conn_01x08_Male; Molex-Mini-Fit-Jr-8-pin-P4.2mm-RowP4.2mm
J2: Conn_01x03_Male; Molex-Mini-Fit-Jr-4-pin-P4.2mm-RowP4.2mm
Q1, Q3: MCT06P10-TP; SOT-223-3_TabPin2
Q2: 2N7002; SOT-23
R1, R6, R7: 2k2; R_1206_3216Metric_Pad1.42x1.75mm_HandSolder
R2, R4, R5: 220k; R_1206_3216Metric_Pad1.42x1.75mm_HandSolder
R3: 22k; R_1206_3216Metric_Pad1.42x1.75mm_HandSolder
U1: NE555; SOIC-8_3.9x4.9mm_P1.27mm
U2: AMS1117-5.0; SOT-223-3_TabPin2
U3: 74LVC1G17; SOT-353_SC-70-5

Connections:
+5V: C1.1, C5.1, C6.1, R2.1, R3.1, U1.8, U2.2, U3.5
+12V: D4.2, J2.1, Q1.3, Q3.3
/VHI: J2.3, R1.2
GND: C1.2, C2.2, C3.2, C4.2, C5.2, C6.2, C7.2, D1.1, D3.2, J1.3, J1.4, J1.7, J1.8, J2.2, Q2.2, R5.2, R7.1, U1.1, U2.1, U3.3
GRN+: D2.2, J1.1, J1.2, Q1.2
unnamed: C2.1, U1.5
unnamed: C3.1, R4.1, U1.2, U1.6
unnamed: C4.1, D4.1, U2.3
unnamed: C7.1, D3.1, R1.1, U3.2
unnamed: D1.2, R6.2
unnamed: D2.1, R7.2
unnamed: Q1.1, U1.4, U3.4
unnamed: Q2.1, R5.1, U1.3
unnamed: Q2.3, Q3.1, R2.2
unnamed: R3.2, R4.2, U1.7
RED+: J1.5, J1.6, Q3.2, R6.1
